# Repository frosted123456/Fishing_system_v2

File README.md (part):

# Ice Fishing Tip-Up Mesh (v2)

Tip-up alarm and per-hole sonar for ice fishing. Each tip-up reports a bite to the chalet box, which rings and
shows everything on its screen and on a phone or PC web page.

| | |
|---|---|
| Firmware | v2, D82 (2026-10-22) |
| Branch | `v2/phase1-mesh-core` |
| Boards | Heltec WiFi LoRa 32 V3, ESP32 WROOM DevKit V1 (30-pin), ESP32-C3 Super Mini (v1 head) |

## Contents

1. [Scope](#1-scope)
2. [System overview](#2-system-overview)
3. [Material](#3-material)
4. [Installation](#4-installation)
5. [Setting up on the ice](#5-setting-up-on-the-ice)
6. [Functions](#6-functions)
7. [Range test](#7-range-test)
8. [How the LoRa airtime is shared](#8-how-the-lora-airtime-is-shared)
9. [Troubleshooting](#9-troubleshooting)
10. [Serial commands](#10-serial-commands)
11. [Repository layout](#11-repository-layout)
12. [Credits](#12-credits)

---

## 1. Scope

Covers building, flashing, wiring, setting up and using the system: tip-ups, hubs, relays and the chalet box.
Not covered: the 3D-printed parts (files kept outside this repo, pictures in 2.1) and the custom sonar board (not built).

**Terms**

| Term | Meaning |
|---|---|
| Chalet box (offshore module) | The Heltec with the screen, buzzer, GPS and CardKB. Runs the network and the web page. Stays in the chalet or is carried on the ice. |
| Hub | A Heltec on the ice with its own hole. Collects the tip-ups around it (its pocket) and sends them to the chalet: ESP-NOW when close, LoRa otherwise. |
| Pocket | A hub and the tip-ups around it (holes within ~50 m). |
| Tip-up | A WROOM board on one hole. Talks ESP-NOW to the nearest hub, sleeps between events. |
| LoRa tip-up | A Heltec on a hole with no pocket around it. Talks LoRa straight to the chalet. |
| Relay | A Heltec that passes a far hub's traffic to the chalet. One hop max. |
| FISH ON | A trip: the spool turned. |

## 2. System overview

| Role | Board | Flash as | Own hole | Sonar |
|---|---|---|---|---|
| Chalet | Heltec V3 | `chalet` | no | no (shows the others) |
| Hub | Heltec V3 | `hub` | yes | optional (`--sonar`) |
| LoRa tip-up | Heltec V3 | `sensor_lora` | yes | optional (`--sonar`) |
| Relay | Heltec V3 | `relay` | no | no |
| Tip-up | ESP32 WROOM | `tipup_wroom` | yes | optional (`--sonar`) |
| Tip-up (v1 head) | ESP32-C3 | `tipup_c3` | yes (reed) | no |

Hub or LoRa tip-up? Same board, same wiring. WROOM tip-ups around it = hub. Alone = LoRa tip-up.

### 2.1 Tip-up pod (3D model)

Printed pod on a Berkley tip-up: battery box with the sonar shield, mast with the board head about 20 cm above the
ice, sliding arm with the Hall sensor, magnet clamp on the shaft. Model v3.0.1, will change.

## 3. Material

### 3.1 Chalet box

| Qty | Item | Note |
|---|---|---|
| 1 | Heltec WiFi LoRa 32 V3 + 915 MHz antenna | OLED is on the board |
| 1 | Active buzzer (CLT1036 or similar) | GPIO7. Passive works too: Settings → Buzzer type |
| 1 | M5Stack CardKB | I2C on GPIO41 (SDA) / GPIO42 (SCL). Optional but needed for the menu and GPS pinning |
| 1 | GPS module, GT-U7 / NEO-6M class | Optional. See 4.4.4 |
| 1 | Small transistor (low-side switch for the GPS GND) | Optional: GPS GND can go straight to GND |
| 1 | 1S LiPo on the Heltec JST, or USB power | Charges from USB-C |

### 3.2 Hub or LoRa tip-up

| Qty | Item | Note |
|---|---|---|
| 1 | Heltec WiFi LoRa 32 V3 + 915 MHz antenna | |
| 1 | 3 × AA Energizer L91 pack with switch | |
| 1 | TPS63020 buck-boost, set to 3.3 V | Feeds the Heltec 3V3 pin |
| 1 | US1881 Hall latch + 4 × N52 magnets | Magnets in the shaft clamp at 45/135/225/315°, poles alternating. Or a reed switch (4.4.5) |
| 1 | 12 mm waterproof push button | Arming button, GPIO5 to GND |
| 2 | 100 k resistors (2:1 divider) | Pack voltage to GPIO2 |
| | Sonar add-on (3.4) | Optional |

### 3.3 WROOM tip-up

| Qty | Item | Note |
|---|---|---|
| 1 | ESP32 WROOM DevKit V1, 30-pin | |
| 1 | 3 × AA Energizer L91 pack with switch | |
| 1 | TPS63020 buck-boost, set to 3.3 V | |
| 1 | US1881 Hall latch + 4 × N52 magnets | Same as the hub |
| 1 | 12 mm waterproof push button | GPIO33 to GND |
| 2 | 100 k resistors (2:1 divider) | Pack voltage to GPIO34 |
| | Sonar add-on (3.4) | Optional |

### 3.4 Sonar add-on (per hole)

| Qty | Item | Note |
|---|---|---|
| 1 | Open Echo TUSS4470 shield 002 | |
| 1 | 200 kHz transducer, BBDM-40200K-DA | 14° beam |
| 1 | **30 V build (4.4.6, what the wiring pictures show):** XL6009 boost module set to 31.5 V + DB107 bridge rectifier + 1N4148 + one 47-100 kΩ resistor + 20 cm of 30 AWG wire (converter enable wire) | ~60 V p-p on the transducer, and the converter is switched off while each ping listens: receiver floor −75 → −86 dB (measured on hub 1). Not an XL6019 (180 kHz switching sits in the sonar band) |
| or 1 | **20 V build:** MT3608 boost, set to 21.5 V | Into J4 middle pin only. 40 V p-p on the transducer, no enable wire. The firmware adapts by itself (4.4.6, mixed fleet) |

### 3.5 Software

| Item | Note |
|---|---|
| VS Code + PlatformIO extension (or `pio` CLI) | Builds and uploads |
| Python 3 | `tools/flash.py` |
| USB-C cable (Heltec), micro-USB (DevKit) | |
| Serial monitor at 115200 | Included in PlatformIO |

## 4. Installation

### 4.1 Get the code

```
git clone https://github.com/frosted123456/Fishing_system_v2
cd Fishing_system_v2
git checkout v2/phase1-mesh-core
```

### 4.2 Cabin Wi-Fi (optional, chalet only)

Copy `src/lora_node/secrets.example.h` to `src/lora_node/secrets.h` and fill in the network name and password.
`secrets.h` is never committed.

Skip it and the chalet runs on its own hotspot. You can also set the Wi-Fi later:

- OLED: Settings → Wi-Fi → Choose network (CardKB)
- Serial: `WIFI:name:password`

### 4.3 Flash a board

1. Plug the board in USB.
2. Open `tools/flash.html` in a browser, pick the board and its job. It gives the command.
3. Run it. Example:

```
python tools/flash.py chalet --id 100 --name "Chalet" --port COM7 --monitor
python tools/flash.py hub --id 1 --name "Pointe" --sonar --gate --port COM8
python tools/flash.py tipup_wroom --id 11 --name "Baie" --sonar --port COM9
```

| Option | Use |
|---|---|
| `--id N` | 1-100, unique on the network |
| `--name "..."` | Name shown everywhere (can be changed later on the page) |
| `--sonar` | Board has the TUSS4470 shield (`tipup_wroom`, `hub`, `sensor_lora`) |
| `--gate` | 30 V build with the converter enable wire (4.4.6): the converter is switched off while each ping listens. Needs `--sonar`. Stays in `devices.ini` for later re-flashes of that board. Leave it out on a board without the wire |
| `--bench` | Bucket test build: sonar runs from boot, `BENCH` line every 2 s (`tipup_wroom`, `hub`). Includes `--sonar` |
| `--build-only` | Build, no upload |
| `--port` | COM port. Leave out and PlatformIO guesses |
| `--monitor` | Open the serial monitor after the upload |
| `--env <name>` | Re-flash a board already in `devices.ini` |

Each board is saved in `devices.ini`. To re-flash the same board: `python tools/flash.py --env hub1_sonar --port COM8`.

ID suggestion: chalet 100, hubs 1-9, tip-ups 11, 12 (pocket 1), 21, 22 (pocket 2)..., relays 90+. A hub's own hole uses the hub's ID.

> **Flash order after a firmware update: every hub and LoRa tip-up first, the chalet last.**

#### 4.3.1 Update a hub without the cable

For a hub that is closed or already on the ice. The first flash with this function has to be over USB.

| Step | Where | What |
|---|---|---|
| 1 | PC | Open `tools/flash.html`, pick the same board, role, node ID and options as the hub runs, tick **Build an update file**, give a folder. Run the command: the file `hub<N>..._date_time.bin` lands in that folder. Copy it to the phone (or do step 3 from the PC) |
| 2 | Hub | Put it in update mode: chalet page, Settings, Advanced, **Firmware update**; or type `OTA` on its serial port; or hold its arming button 3 s while switching it on. Its screen shows the hotspot name |
| 3 | Phone | Join the hotspot `IceFish-Hub<N>-UPDATE` (same password as the others), open `http://192.168.4.1`, pick the file, **Send and restart** |

In update mode the hub does nothing else: no sonar, no alerts, no radio. It leaves the mode by itself after 10 minutes
without an upload. The running firmware is kept in the other slot: a file built for another board (other node ID or
role) is refused, and a new firmware that does not stay up 90 s in three starts is abandoned for the old one. The
chalet box has a single firmware slot (map storage took the other) and is still updated over USB; the tip-ups too.

### 4.4 Wiring

#### 4.4.1 WROOM tip-up + shield 002

| # | ESP32 DevKit V1 | Shield 002 | Signal |
|---|---|---|---|
| 1 | **3V3** (TPS63020 3.3 V) | **5V** pin | TUSS4470 VDD. **Never 5 V.** |
| 2 | GND | GND | Common ground (pack, TPS63020, boost module, ESP32, shield) |
| 3 | D18 | D13 | SCLK |
| 4 | D19 | D12 | SDO → MISO |
| 5 | D23 | D11 | MOSI → SDI |
| 6 | D5 | D10 | NCS |
| 7 | D26 | D8 | IO1 |
| 8 | D25 | D9 | IO2 (burst) |
| 9 | VP (GPIO36) | A0 | VOUT echo. Twist with its own GND wire |
| 10 | - | **J4 middle pin**, no jumper on J4 | Boost output + (wire A): XL6009 at 31.5 V, or MT3608 at 21.5 V. Boost GND to shield GND |
| 11 | - | **C6, the pad nearer the TUSS4470** | 30 V build only: wire B from the XL6009 output through DB107 + 1N4148, and the bleed resistor across C6 (4.4.6) |
| - | not wired | D2, D3, RESET, AREF, 3.3V, VIN | |

Other WROOM connections:

| Pin | To |
|---|---|
| GPIO27 | Hall latch OUT. US1881 VDD from the **pack**, not 3.3 V |
| GPIO33 | Arming button to GND (no resistor) |
| GPIO34 | 2:1 divider from the pack |
| GPIO2 | LED (on the DevKit) |
| D13 (GPIO13) | 30 V build: converter enable wire to the XL6009's chip pin 2 (4.4.6). Flash with `--gate`. Not yet tried on a WROOM |

#### 4.4.2 Heltec V3 + shield 002 (hub, LoRa tip-up)

| # | Heltec V3 | Shield 002 | Signal |
|---|---|---|---|
| 1 | **3.3V** pin | **5V** pin | TUSS4470 VDD. **Never 5 V.** |
| 2 | GND | GND | Common ground |
| 3 | GPIO47 | D13 | SCLK |
| 4 | GPIO33 | D12 | SDO → MISO |
| 5 | GPIO48 | D11 | MOSI → SDI |
| 6 | GPIO34 | D10 | NCS |
| 7 | GPIO38 | D8 | IO1 |
| 8 | GPIO39 | D9 | IO2 (burst) |
| 9 | GPIO6 | A0 | VOUT echo. Twist with its own GND wire |
| 10 | - | **J4 middle pin**, no jumper on J4 | Boost output + (wire A): XL6009 at 31.5 V, or MT3608 at 21.5 V. Boost input from the pack |
| 11 | - | **C6, the pad nearer the TUSS4470** | 30 V build only: wire B from the XL6009 output through DB107 + 1N4148, and the bleed resistor across C6 (4.4.6) |
| - | not wired | D2, D3, RESET, AREF, 3.3V, VIN | |

Other Heltec connections:

| Pin | To |
|---|---|
| 3.3V pin | TPS63020 3.3 V output |
| GPIO4 | Hall latch OUT (or reed, 4.4.5). US1881 VDD from the pack |
| GPIO5 | Arming button to GND |
| GPIO2 | 2:1 divider from the pack (not the onboard VBAT pin) |
| GPIO7 | Buzzer (optional on a hub) |
| GPIO40 | 30 V build: converter enable wire to the XL6009's chip pin 2 (4.4.6). Flash with `--gate` |

Turn the pack off when USB is plugged in.

#### 4.4.3 Shield 002 set-up

- Frequency jumpers: **JP3 + JP4 only** (200 kHz). JP1, JP2, JP5, JP6 open.
- Transducer: cable shield → **top** pin, signal → bottom pin.
- Boost output into the **J4 middle pin** only. Not VIN, not the XT30.
- 30 V build: XL6009 at **31.5 V**, wire B, bleed resistor and enable wire, see 4.4.6.
- 20 V build: MT3608 at **21.5 V** (max ~22 V), nothing else.
- Optional: remove R3 (power LED).

#### 4.4.4 Chalet box (offshore module)

| # | Heltec V3 | To | Signal |
|---|---|---|---|
| 1 | JST battery | 1S LiPo 3.7 V | Power. Charges from USB-C |
| 2 | 3.3V pin | GPS VCC, CardKB VCC | 3.3 V out |
| 3 | GND | GPS switch, CardKB GND, buzzer − | Common ground |
| 4 | GPIO48 | GPS TXD | GPS → Heltec (9600 baud) |
| 5 | GPIO47 | GPS RXD | Heltec → GPS |
| 6 | GPIO26 | Transistor gate/base | GPS power on (driven high). GPIO46 is driven too |
| 7 | GPIO41 | CardKB SDA | I2C |
| 8 | GPIO42 | CardKB SCL | I2C |
| 9 | GPIO7 | Buzzer + | Active buzzer (CLT1036) |
| - | GPIO2, 4, 5 | not wired | Hole sensor, button and divider are for hubs only |

On the board, nothing to wire: PRG button (GPIO0), OLED, LoRa radio, battery reading (GPIO1/37), LED.

- CardKB VCC on 3.3 V is est.: check your box (the CardKB also takes 5 V).
- GPS GND straight to GND (no transistor): build with `-D GPS_EN_PIN=-1`.
- No GPS: build with `-D GPS_RX_PIN=-1`.
- GPS on other pins: the chalet scans the free header pins at boot and keeps the one that answers.

#### 4.4.5 Reed switch instead of the Hall sensor

A reed switch can replace the Hall latch to detect FISH ON. The code is still active (the C3 tip-up uses it).

| Board | Wire | Build flag (add to the board in `devices.ini`) | Polarity |
|---|---|---|---|
| Heltec hub / LoRa tip-up | Reed between GPIO4 and GND | `-D HOLE_HALL_LATCH=0` | OLED Settings → Reed polarity |
| WROOM tip-up | Reed between GPIO27 and GND | `-D HALL_LATCH=0` | `REED_ACTIVE_HIGH` in `src/sensor_node/config.h` |
| C3 tip-up | Reed between GPIO4 and GND | none (reed by default) | `REED_ACTIVE_HIGH` |

Default polarity: trips when the pin goes HIGH (contact opens). With a reed, the trip follows the switch level, not
spool turns.

#### 4.4.6 30 V drive and converter enable wire (external VDRV, knob `vmode 2`)

Two changes that go together. They are the build the wiring pictures of 4.4.1 and 4.4.2 show.

- **30 V drive.** The TUSS4470's own drive regulator stops at 20 V (40 V p-p). Feeding its VDRV pin from outside at
  ~30 V gives ~60 V p-p on the transducer, **+3 to +4.6 dB (est.)**. No new board; `vmode 2` is the default.
- **Converter enable wire.** The XL6009 switches at 400 kHz and the receiver hears it at −75 dB. One wire from an ESP32
  pin to the converter's enable pin lets the firmware switch it off while each ping listens: receiver floor **−86 dB**
  in water, with no loss of transmit strength (measured on hub 1, 14 Nov 2026, D179).

| # | From | To | Note |
|---|---|---|---|
| 1 | Pack + / GND | XL6009 IN + / IN − | Replaces the MT3608. **Set the output to 31.5 V with a meter before connecting anything** |
| 2 | XL6009 OUT + | Shield **J4 middle pin** (wire A) | Same pin as the MT3608 today; no jumper on J4. Becomes VPWR ≈ 30.7 V after the shield's 1N4001 |
| 3 | XL6009 OUT + | DB107 **−** leg | DB107: use only − and +, cut the two ~ legs |
| 4 | DB107 **+** leg → **1N4148** (stripe toward C6) | Shield **C6, the pad closer to the TUSS4470** (wire B) | VDRV ≈ 29.6 V. The other C6 pad is GND (beeps to ground) |
| 5 | XL6009 OUT − | Shield GND | Common ground |
| 6 | Shield **C6, the pad closer to the TUSS4470** | The **other C6 pad** (GND), through a **47-100 kΩ resistor** soldered across C6, pad to pad (bleed) | Drains C6 when the power goes off, see below. Draws 0.3-0.65 mA at 30 V (about 3-7 mA from the pack, est.) |
| 7 | XL6009 **chip pin 2** (EN), cut free of its pad | Heltec **GPIO40** / WROOM **D13** (enable wire, 30 AWG, no resistor) | See "Converter enable wire" below. Flash with `--gate` |

Rule: **VPWR > VDRV + 0.3 V at all times, power-up included** (datasheet 6.3 note / 7.3.1: otherwise reverse current
flows from VDRV into VPWR). VPWR draws only 150-340 µA, so the shield's 1N4001 drops just ~0.45-0.5 V; VDRV idles at
microamps, where the DB107's two diodes drop only ~0.7-0.8 V (est.): ~0.25 V gap, too tight. The 1N4148 adds ~0.4-0.6 V:
**~0.7-1 V gap** for ~−0.2 dB. Never wire B without the DB107 + 1N4148.

Power-off (D143): the diodes of wire B stop C6 from discharging backwards, and nothing loads VDRV in this mode, while
VPWR follows the boost output down. Without the bleed resistor (row 6) VDRV stays near 30 V with VPWR falling under it
at every switch-off: the reverse-current case of the rule above. With 47-100 kΩ, C6 empties in 0.1-0.2 s, faster than the
boost output falls. The bleed also keeps 0.3-0.65 mA flowing in the DB107 + 1N4148 while idle, so their drop is a real
~1.5 V (est.) instead of a microamp-level one: the gap no longer depends on leakage. It has no effect on a ping.

Pads on the shield (from the board file `referance/shield002_tmp/TUSS4470_shield.kicad_pcb`): C6 lower pad = VDRV,
C6 upper pad = GND, R1 lower pad = VPWR (an easier meter point than C7).

**Converter enable wire** (D170 to D179). The usual XL6009 module (XL6009E1, 47 µH, 100 µF output, 330 Ω + 10 k trimmer
feedback) has no enable pad: chip pin 2 (EN) is tied to VIN on the board.

1. Meter check: legs toward you, chip seen from the top, pins are 1 GND, 2 EN, 3 SW, 4 VIN, 5 FB. Pin 2 beeps to pin 4.
2. Cut pin 2 free of its pad (or unsolder and lift it). It must no longer beep to pin 4.
3. Solder a thin wire (30 AWG) from the lifted pin to **GPIO40** (Heltec) or **D13** (WROOM). No resistor (a large
   series resistor may not pull the pin low enough against its internal pull-up).
4. Flash with `--gate`: the firmware then drives the pin HIGH while the sonar runs and LOW in sleep. **Do not leave the
   wire on a board flashed without `--gate`:** the pin then floats, and on Hole 2's module a floating enable left the
   converter off (output at the pack voltage, wiring check "VDRV NOT READY"), although the datasheet says floating = on.
5. Web page → Settings → Advanced → Wiring check: **Converter enable wire OK, noise floor N dB lower with the converter
   switched off** (hub 1: 14 dB or more). `NO EFFECT` = the pin is still tied to VIN, or the wire is on another GPIO.
6. Bench build: the **Converter off 6 s** button holds the converter off: the transmit fades within 1-2 s and comes back
   (the pack voltage still reaches the driver through the converter's coil and diode, so the strongest echoes stay). The
   **Noise scan** button records the receiver floor with the converter running and gated, step by step.

What the firmware does with the wire: converter off 0.3 ms before each burst, on again after the last sample of its
listening window (about 21 ms), so the 100 µF output capacitor has lost nothing when the burst fires; in sleep the
converter stays off. The rule VDRV below VPWR holds: both follow the same rail. Not yet tried on a WROOM (same driver).

Battery (est., from the module's parts): the feedback divider alone draws 3.8 mA at 30 V and the bleed 0.3-0.65 mA; with
the chip's 2.5-5 mA that is about 35-40 mA from the pack while the converter runs, against ~2-3 mA for the MT3608. With
the enable wire the converter is off whenever the board sleeps (about 0.5 mA left through the divider). Datasheet
minimum input 3.6 V: the end of the pack.

Bring-up:

1. Meter, diode mode: DB107 − to + reads 1.0-1.3 V, reversed OL.
2. **Check the gap before wire B touches C6.** Connect wire A only, power on, sonar pinging (`vmode 0`, the chip makes
   its own 20 V: safe). Measure VPWR on the **C7** pad that is not GND (small capacitor just left of C6). Measure the
   1N4148 end of the DB107 chain, unconnected (worst case: no current). Gap = VPWR − that end. **≥ 0.5 V: connect wire B.** Less: add
   a second 1N4148.
   Then wire B on: C6 pad must read below C7.
3. `vmode 2` is the default since D147 (nothing to set after a flash; the Water presets do not touch it).
   Then the enable wire, steps 1 to 5 above.
4. Bench line: no `BURST FAULT`. `ring=` a bit longer: raise `dead` one step if needed. (No `VDRV LOW` in this mode.)
5. Gain check: measure echo **minus floor** (bottom, a weight) **before wire B goes on** (20 V drive) and after
   (`vmode 2`): expect +3 to +4.6 dB. With wire B connected, `vmode 0` does NOT go back to 20 V.

**Mixed fleet** (knobs are global: the hub broadcasts the same `vmode` to every pod). The enable wire is per board
(`--gate`): a board flashed without it simply leaves its converter running. `vmode 2` on a pod WITHOUT wire B
leaves its VDRV unpowered (weak pings). Since D163 such a board notices it by itself (no transmit seen on 8 pings in a
row), prints `SONAR: no transmit seen in external-VDRV mode` and runs on the chip's regulator until the next boot
(written from the datasheet behaviour, **not yet tried on a board without wire B**). If an unmodded pod still pings
weakly, keep **`vmode 0` everywhere**: modded pods
still drive at ~30 V (the chip's 20 V regulator only charges and stays off above its target; inferred, confirm once:
same echo, no `BURST FAULT` with `vmode 0` and `vmode 2` on a modded hub). WROOM pods: same shield, same wiring, knobs
from the hub; `TUNE` runs on the Heltec only.

Limits: chip 36 V max (40 V absolute), C6 rated 40 V, XL6009 output caps often 35 V: stay at **31.5 V**.
Back to 20 V: `vmode 0` **and** unplug wire B (with wire B in place VDRV stays ~30 V; safe, not 20 V).
The XL6009 must still make ≥ 29 V on a half-used pack; if not, keep the MT3608 at 12 V in front of it.

### 4.5 Bench check

| Step | Do | Expect |
|---|---|---|
| 1 | Power the chalet alone | Boot screen, then Home |
| 2 | Power a hub | Chalet Home shows the pocket within a few seconds |
| 3 | Power a tip-up | 2 quick blinks at boot. It starts armed |
| 4 | Turn the spool a quarter turn | FISH ON on the chalet, buzzer, phone |
| 5 | Web page → Settings → Advanced → Wiring check → Run | Sensor, button, battery, sonar shield, radio OK. A sleeping tip-up answers within 1 min. 30 V build with `--gate`: "Converter enable wire OK" |
| 6 | Sonar holes: flash with `--bench`, transducer in a bucket | `BENCH` line every 2 s on serial, bottom found |

## 5. Setting up on the ice

1. Mount every board **at least 20 cm above the ice**.
2. Turn on the devices in any order as you set the holes. The chalet shows "SETUP" until a hub has been in for
   5 min (10 min max after boot). That is normal.
3. Check every hole is armed (no DISARMED on the page or OLED). Holes keep their armed state across reboots.
4. Connect the phone (6.3).
5. Place the holes on the map:
   - With GPS: carry the chalet box to each hole, OLED → GPS / pin holes, select the hole, Enter.
     Or on the page: tap the hole → **Pin here**.
   - Without GPS: on the page, tap the hole → **Tap the map**.
6. Set the bait depth of each sonar hole: tap the hole → bait.
7. Check bait: disarm the hole first (short press), re-arm after.
8. Fresh battery pack in a hub or tip-up: hold its arming button while switching the pack on, until the LED blinks 3
   times (~3 s), or on the chalet page: Test tab → **Battery packs** → **New pack** on that hole. That sets its pack
   hours back to 0. **Read all holes** there shows every hub and tip-up (flagged past 12 h); the hub OLED shows its own
   at the top right (`Pk7.3h`); `PACK` on serial or the bench page too. Released sooner = ordinary start.

**Battery (3 × L91 per module, est. from datasheets, D205):** about 15-24 h per pack at 20 °C, 11-21 h at -15/-20 °C,
about 10 h with the bench page streaming. Plan one fresh pack per module per session plus one spare. The L91 voltage
stays flat until the last 10-15 %, so the pack hours, not a voltage, are the gauge; a meter on the 10 A range in
series with the pack gives the real figure (hours = ~13 Wh / pack watts).

The first time, the map origin is set by itself once the chalet GPS is steady for 30 s. It is kept after that.
To move it: OLED GPS page → Chalet here, or tap the chalet on the map → **Chalet here**. Pinning a hole needs a GPS
fix and an origin.

## 6. Functions

### 6.1 Tip-up

| Action | Result | LED |
|---|---|---|
| Short press | Arm / disarm | Armed: 2 short. Disarmed: 1 long |
| Short press while tripped | Clear the trip | 1 short |
| Hold 3 s | Send a status report now | 3 short |
| Held while switching the pack on, ~3 s | New pack: pack hours back to 0 (D205) | 3 blinks |
| Spool turns a quarter turn | FISH ON | |
| Spool still for 30 s | Line back to normal on the tip-up | |

A disarmed hole ignores the spool (use it to check the bait). Disarming a tripped hole also clears the alarm on
the chalet. Clearing a trip at the hole does not: the chalet keeps ringing until silenced.

Holes start armed and keep their state across reboots. The hub and LoRa tip-up button (GPIO5) works the same,
with the white LED and a short chirp. LED also blinks once per status sent and 3 times per alert sent.

### 6.2 Chalet box and hubs (OLED)

**PRG button**

| Press | Chalet | Hub |
|---|---|---|
| Short | Next page. During FISH ON: silence. Screen asleep: wake it | Same |
| Double | Page action (written at the bottom). On Home: unsilence | Same |
| Hold 3 s | Connect phone page | Hotspot on/off (30 min, +5 min while a phone is on it) |
| Hold 10 s | Network reset (link, channel and relays back to default; names, alerts and Wi-Fi kept) | Same |

A bar shows what releasing will do (from 1 s). Pages go back to Home after 60 s (Settings 3 min). The screen
sleeps after 5 min and wakes on FISH ON or any press. GPS pinning and Wi-Fi options need the CardKB.

**CardKB (chalet)**

| Key | Does |
|---|---|
| Esc | Menu. In a page: back to the menu |
| ← / → | Previous / next page |
| ↑ / ↓ | Inside the page (more holes, next hole, list) |
| Enter | Page action ("OK: ..." at the bottom) |
| Space / Tab / n, p | Next / previous page |
| + / − / a | Sonar and Focus: depth scale (a = auto) |
| S | Silence on/off |
| Any key during FISH ON | Silence |
| Del, twice | GPS page: clear the selected hole's position |

**Pages**

| | |
|---|---|
|  | **Menu** (Esc). All pages. |
|  | **Home**. Holes online, one row per pocket (filled = OK, hollow = offline, half = low battery, X = sensor fault, blinking = FISH ON). Link per pocket: OK (LoRa), ESP-NOW, n off, LOST. Footer: near bait, battery low, range test. |
|  | **FISH ON**. Takes over every page, blinks until silenced. |
|  | **Holes**. 4 per page: name, fish seen by the sonar, battery. ↑ / ↓ for more. |
|  | **Sonar**. One column per sonar hole: bottom, fish (bars), bait (tick). |
|  | **Focus**. Fish finder of the watched hole, last ~30 s. ↑ / ↓ = other hole. |
|  | **GPS / pin holes**. Chalet here = map origin. Select a hole, Enter = pin it where the box is. |
|  | **Network**. Link, LoRa channel and activity, signal of each hub (E = via ESP-NOW). |
| | **Test / simulation**. Holes running fake sonar or fake trips, radio test. |
|  | **Connect phone**. Wi-Fi name, password and address. |
|  | **Settings**. Wi-Fi, buzzer, near-bait beep, alarm, LoRa channel, simulation, sonar filter, display, network reset, reboot. |
|  | **Hub Home**. Link to the chalet, its holes and battery. Hub pages: Home, Holes, Network, Connect, Settings (hotspot, buzzer, alarm, ESP-NOW relay, reed polarity, network reset, reboot). |
|  | **Hub Connect**. Hold PRG 3 s to turn the hub hotspot on. |

### 6.3 Web page

**Connect**

| Where | Wi-Fi | Address |
|---|---|---|
| Chalet hotspot | `IceFish-Remote`, password `fishon123` | http://192.168.4.1 |
| Cabin Wi-Fi (secrets.h or Settings → Wi-Fi) | Same network as the chalet | The address on the OLED Connect page, or http://icefish.local |
| Hub hotspot (hold PRG 3 s) | `IceFish-Hub<N>`, password `fishon123` | http://192.168.4.1 |

`icefish.local` works on most PCs and iPhones. Some Android phones need the number address.

Works in a phone or PC browser. Tap once on the page to allow the alert sound.

On every tab: status line, **Sound on/off**, **Silence alerts**, and a red FISH ON bar at the bottom with the hole names.

**Holes tab**

| Item | Does |
|---|---|
| Pocket map | Drag to pan, pinch or +/− to zoom, ⌂ = back to the chalet, ⤢ = full screen |
| Map / Satellite | Background (needs internet on the phone, or a saved area) |
| Depth | CHS bathymetry where it exists |
| Save area | Keeps the tiles of what you see on the chalet, for any phone on the ice |
| Cyan ring | Hole being followed (see Sonar tab). Arrow = it just moved there. Padlock = your pick |
| Tap a hole | Sheet: bottom, fish, bait, line out, battery, link, distance. Arm / Disarm, bait, Watch sonar, Pin here, Move, Remove |
| Tap the chalet | Chalet here, clear all positions |
| Live card | Beside the map: the whole water column of every streaming hole, newest on the right. Bottom, fish, bait line. Follow the action button and the 1 / 2 / 3 picker: how many holes stream at once (more = more radio, slower page). Tap a panel for the full view on the Sonar tab |
| Hole cards | Folded under the Live card. State, battery, link, last minutes of sonar. Watch, Set bait, Arm / Disarm, Rename |

**Sonar tab**

| Item | Does |
|---|---|
| Follow the action | On by default. The live view goes to the hole with the most action. FISH ON wins for 2 min. Up to 2 more holes stream at the same time when the radio has room ("LIVE too") |
| Hole cards on top | Every sonar hole with its water-column preview. Tap one to watch it live; your pick stays 5 min, then Follow takes over again |
| Flasher | Live, about 1 s behind. Pause to freeze |
| Last 60 seconds | Waterfall, 4 pings per second. With **Raw echogram** on (Display, default on), the hole you watch also sends its raw ping once a second (the HD line: 2.5 cm cells at any depth, 1 dB steps near the noise floor) with a crisp mark for each echo (up to 12, at its exact depth; in a hole deeper than 6 m the marks cover the bottom 6 m), and the waterfall shows it underneath the detector's marks, like a fish finder: an echo the detector did not report is still visible. Water (anything under the **Weak echoes** level: 4 / 8 / 12 / 20 dB over the floor; full colour at 40 dB) stays dark, the blind zone is a flat grey band, below the bottom is dimmed (second bottom echo, barrel walls). A still object (a hanging ball, a stump) is reported as a mark for a few seconds only, then becomes part of the still scene; the raw echogram keeps showing it. Off: only what the detector reported |
| ft / m | Depth units on this phone |
| Display | Depth scale, colour gain, weak echoes |
| Processing | Noise filter, water type (lake / shallow / bucket), Advanced, Defaults, Send to holes again |
| Sonar test mode | Fake sonar on the test holes |

**Radio tab**

| Item | Does |
|---|---|
| Links | When the chalet last heard each hub on LoRa and ESP-NOW |
| Range test | See section 7 |
| Radio test modes | Fixed or rotating speed for every hub, adaptive speed (on by default), reset stats |
| Hubs | Speed (SF) used per hub, packets, signal |

**Settings tab**

| Section | Contains |
|---|---|
| Alerts | Chalet buzzer, near-bait beep, FISH ON alarm: until silenced, or 1, 5, 15, 30 min after the trip |
| PIN | Optional 4-8 digit PIN for any change from the page. Silence and Watch never need it |
| Network | Wi-Fi state, link, channel |
| This phone | Alert sound, depth units, sound test |
| Advanced | Line per spool turn, beam angle, wiring check, map storage, LoRa channel, relays, test and simulation |
| About | Version |

Forgot the PIN: serial `PIN CLEAR`.

**Wi-Fi tab**

The chalet keeps up to 4 networks with their passwords (house, parents, cabin). Saved networks: one tap on Connect
switches the chalet; ✕ forgets one. Add a network: name and password, or Scan and tap Use on a network around.
When the network in use is not found, the chalet joins the strongest saved one by itself within a minute or two
(first retry after boot, then every 5 min). Passwords never come back to the page. If your phone is on the cabin
network when you switch, the page comes back at `http://icefish.local` or on the hotspot.

### 6.4 Alerts

| Event | Chalet | Phone |
|---|---|---|
| FISH ON | Screen, buzzer | FISH ON bar, beep |
| Silence (button, key or page) | Sound stops. Holes already back to normal are cleared. A hole still out rings again after 5 min | Same on every phone |
| Line back to normal | Keeps ringing until silenced (default) or the alarm time in Settings | |
| New trip | Always rings, even during a silence | |

### 6.5 Map offline

At home with internet: open the Holes tab, move to the lake, zoom in, **Save area**. The tiles stay on the chalet
(up to ~4.8 MB, shared with the depth pack and range test runs). Tiles seen on a phone also stay on that phone.

Depth contours (optional, PC):

```
pip install numpy rasterio matplotlib pyproj
python tools/lake_prep.py --bbox 45.40 -75.80 45.55 -75.60 --nonna --name "Ottawa-Gatineau" --out season.json
```

Then Settings → Advanced → Map storage → Store on chalet.

## 7. Range test

LoRa only. Gives the success rate of each speed (SF9 to SF5) against distance. SF6 and SF5 need the hub on
firmware D80; older hubs test SF9 to SF7 only.

1. Put the chalet box next to the hub that stays put. It must reach the chalet directly and not relay another hub.
2. Web page → Radio → Range test. Pick the hub.
3. Press **Box is at the hub: pin it here** (needs a GPS fix and the map origin set).
4. Add a note if you want (ice, antenna height...). Press **Start the range test**.
5. Walk away with the box. The banner shows the run on every tab, and the OLED Home footer shows `RANGE <distance> SF<n> ok/--`.
6. Press **Stop**, then **Download CSV**.

The run stops by itself after 2 h, if the hub is not heard for 5 min, or if storage is low. 30 runs max: download
and delete old ones. The other hubs keep working during the test.

During a run the hub-to-chalet link is forced to LoRa (the Radio tab shows it), then goes back to the setting at
stop. Without that, a hub next to the chalet talks ESP-NOW, keeps its LoRa radio idle, and every row reads `ok 0`.
A side-by-side check should show `ok 1` on all five speeds with an RSSI around -20 to -40 dBm within a minute of
starting (the hub needs a few seconds to switch over).

CSV columns: `t_s, utc, lat, lon, sats, hdop, dist_m, frame, mode, ok, crc, rssi_dbm, snr_db, hub_beacon_rssi, hub_beacon_snr, hub_beacon_lost64`.

## 8. How the LoRa airtime is shared

One LoRa channel, one frame of 0.5 s (it stretches to 1, 1.5 or 2 s by itself when the turns don't fit). The chalet
sends a beacon at the start of each frame with the turn of every hub: when, how long, how many bytes, at what
speed. Hubs only transmit in their turn. WROOM tip-ups use ESP-NOW
to their hub, which costs no LoRa time: the hub packs its whole pocket into its own turn.

| Part of the frame | What it is |
|---|---|
| beacon | Chalet → everyone. The plan for this frame, the watched hole, commands |
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
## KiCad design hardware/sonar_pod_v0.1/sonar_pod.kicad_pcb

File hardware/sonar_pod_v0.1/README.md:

# Sonar pod board v0.1 — generated design (NOT ordered, NOT reviewed by a human yet)

TUSS4470 front end (net-for-net from Open Echo `shield_003`, 200 kHz values fixed) + MT3608 boost 22 V for VPWR
(EN from the head, pulled up) + TPS63020 3.3 V + sense dividers + one 16-wire cable to the ESP32 in the head.
52 x 43 mm, 2 layers, all SMD on top, 4 x M3. Made with KiCad 7 tools (opens in KiCad 10).

| File | What |
|---|---|
| `sonar_pod.kicad_pro/.kicad_sch` | schematic, label style (every pin ends in a global label, no wires) |
| `sonar_pod.kicad_pcb` | routed board (freerouting), zones filled, DRC: 0 unconnected, 0 clearance |
| `sonar_pod_schematic.pdf`, `routed_f.png`, `routed_b.png` | previews |
| `sonar_pod_gerbers.zip` | gerbers + drill for JLCPCB |
| `sonar_pod_bom_jlcpcb.csv`, `sonar_pod_cpl_jlcpcb.csv` | assembly BOM (LCSC numbers) and pick-and-place |
| `sonar_pod.step` | 3D (library models only) |
| `src/design.py` | the single source: parts, pins, nets, positions. `make_pcb.py`, `make_sch.py`, `route.sh` regenerate everything |

## Head cable J4 (JST-PH 2.0 mm, 16)
1 3V3 · 2 GND · 3 GND · 4 NCS · 5 SCLK · 6 SDI · 7 SDO · 8 IO1 · 9 IO2 · 10 VOUT · 11 OUT4 · 12 HALL · 13 BOOST_EN · 14 VBAT_ADC · 15 NTC_ADC · 16 VPWR_ADC
ESP32 DevKit V1 side (proposal): NCS 5, SCLK 18, SDI 23 (MOSI), SDO 19 (MISO), IO1 26, IO2 25, VOUT 36, OUT4 32, HALL 27, BOOST_EN 33, VBAT_ADC 35, NTC_ADC 39, VPWR_ADC 34.

## Other connectors
J1 battery (XH 2): + −. J2 transducer (XH 5): A, B, shield(SGND), NTC, NTC-gnd. J3 hall (XH 3): 3V3, GND, OUT.

## Design notes
- VBOOST = 0.6 V x (1 + 360k/10k) = 22.2 V. Knob `vdrv` 20 (VPWR > VDRV + 0.3 V). TVS SMAJ24A on the rail.
- MT3608 EN: 100k pull-up to VB, J4.13 pulls it low to cut the sonar rail (sleep). Boost off = TUSS4470 unpowered: re-init after wake.
- TPS63020: EN = VIN (always on), PS/SYNC = GND (power save on), VINA via 10 R + 100 nF, 1.5 uH XFL4020, 2 x 10 uF in, 3 x 22 uF out, FB 1M/180k.
- Receive: R_INP 200 R 1206 + C_INP 330 pF -> INP; C_INN 22 nF to SGND; C_FLT 3.3 nF to SGND; spare DNP footprints C18/C19 for tuning.
  SGND island (F.Cu) joined to GND through FB1 ferrite (R9 0 R DNP alternative). Transducer shield pin on SGND.
- VOUT to the cable through 100 R + 1 nF. VBAT/2 and VPWR x 10/85 dividers, NTC 10k pull-up.
- Reverse battery: AO3401A P-FET high side, gate to GND through 100k.

## VERIFY BEFORE ORDERING (things I could not check from here)
1. U2 footprint `Texas_DSJ0014A` is GENERATED (pads +-1.45 mm, 0.85 x 0.28, EP 1.6 x 2.6, pins 1-7 left top->bottom,
   8-14 right bottom->top). Compare with the TI DSJ0014A drawing / KiCad 10 library and replace if KiCad 10 has it.
2. D1 (K=1 to VBOOST, A=2 to SW) and D2 (K=1 to VBOOST, A=2 to GND) polarity against the SMA / SOD-123W footprint pad 1.
3. JST pin-1 orientation on J1-J4 against the housings you crimp.
4. L1 saturation current (>1.5 A at 22 V boost from 3.6 V), L2 >4 A. LCSC numbers for L1/L2/FB1/D2/D3/J1-J4 were typed from memory: check each on lcsc.com.
5. Routing is freerouting's: look at the boost loop (L1-U3-D1-C8) and the INP/INN traces in KiCad; shorten by hand if they wander.
6. Silkscreen: 20 overlap warnings (reference text over pads) — cosmetic, clean up or let JLC strip them.
7. ESP32 ADC pins: 34/35/36/39 are input only (fine for ADC), 32/33 are output capable.

## Rough cost (JLCPCB, 5 boards, estimate — verify in the JLC quote)
PCB 5 x 52x43 2-layer ~ $4 · assembly setup + stencil ~ $10 · extended-part fees ~ 8 x $3 = $24 ·
parts ~ $9/board (TUSS4470 $3.1, TPS63020 ~$2.5, inductors ~$0.8, connectors ~$0.7, rest ~$2) x 5 = $45 · shipping ~ $20
=> about $100-120 for 5 assembled boards, ~$22 each. The shield + 2 modules route is ~$40-45 per tip-up.

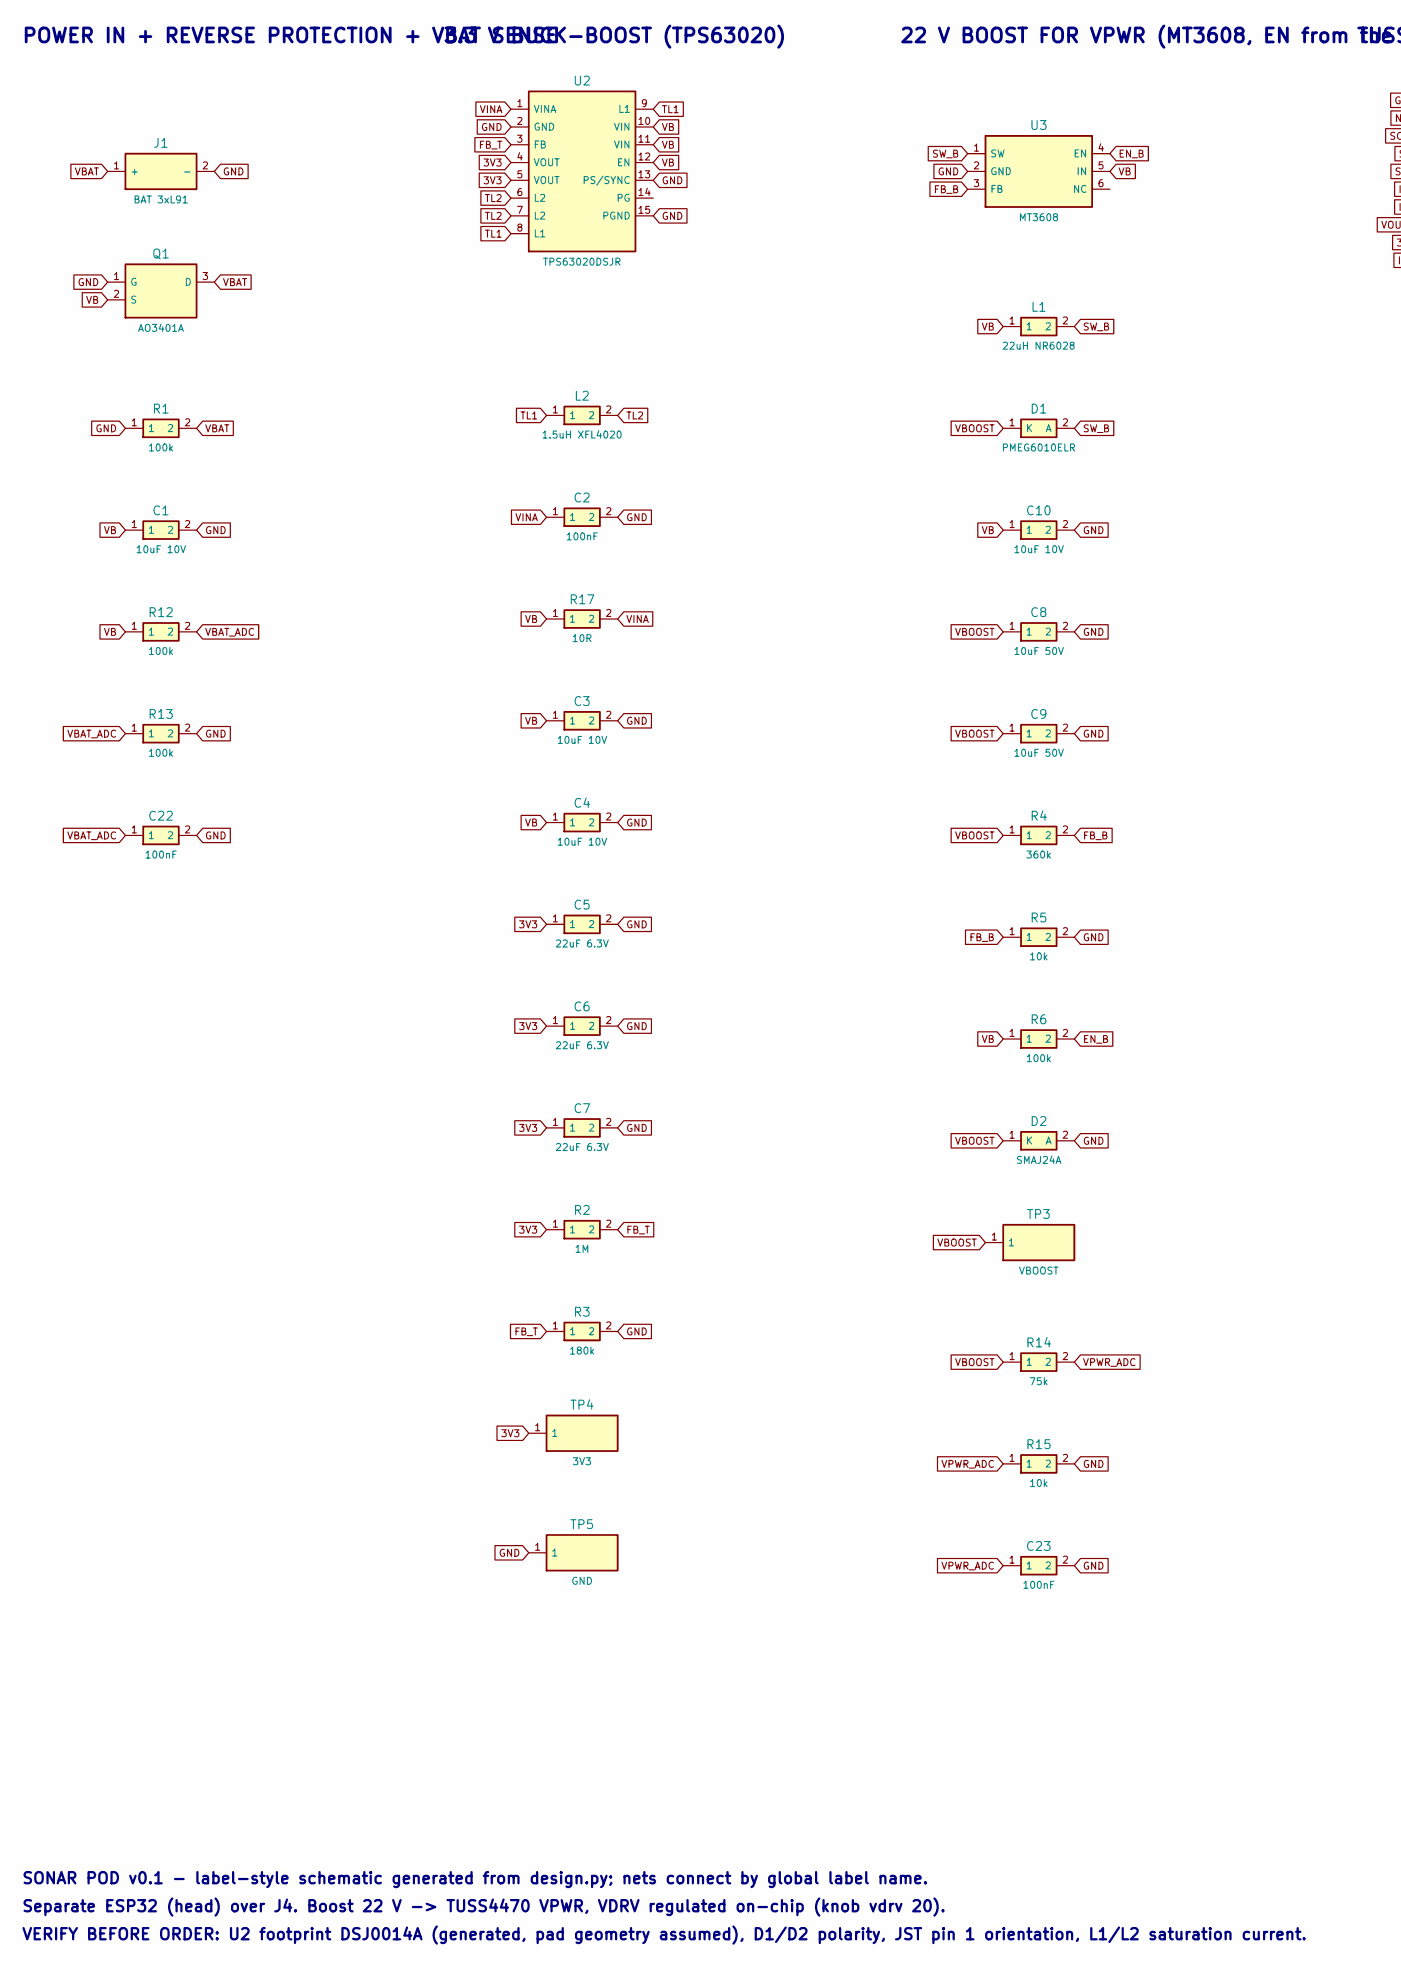
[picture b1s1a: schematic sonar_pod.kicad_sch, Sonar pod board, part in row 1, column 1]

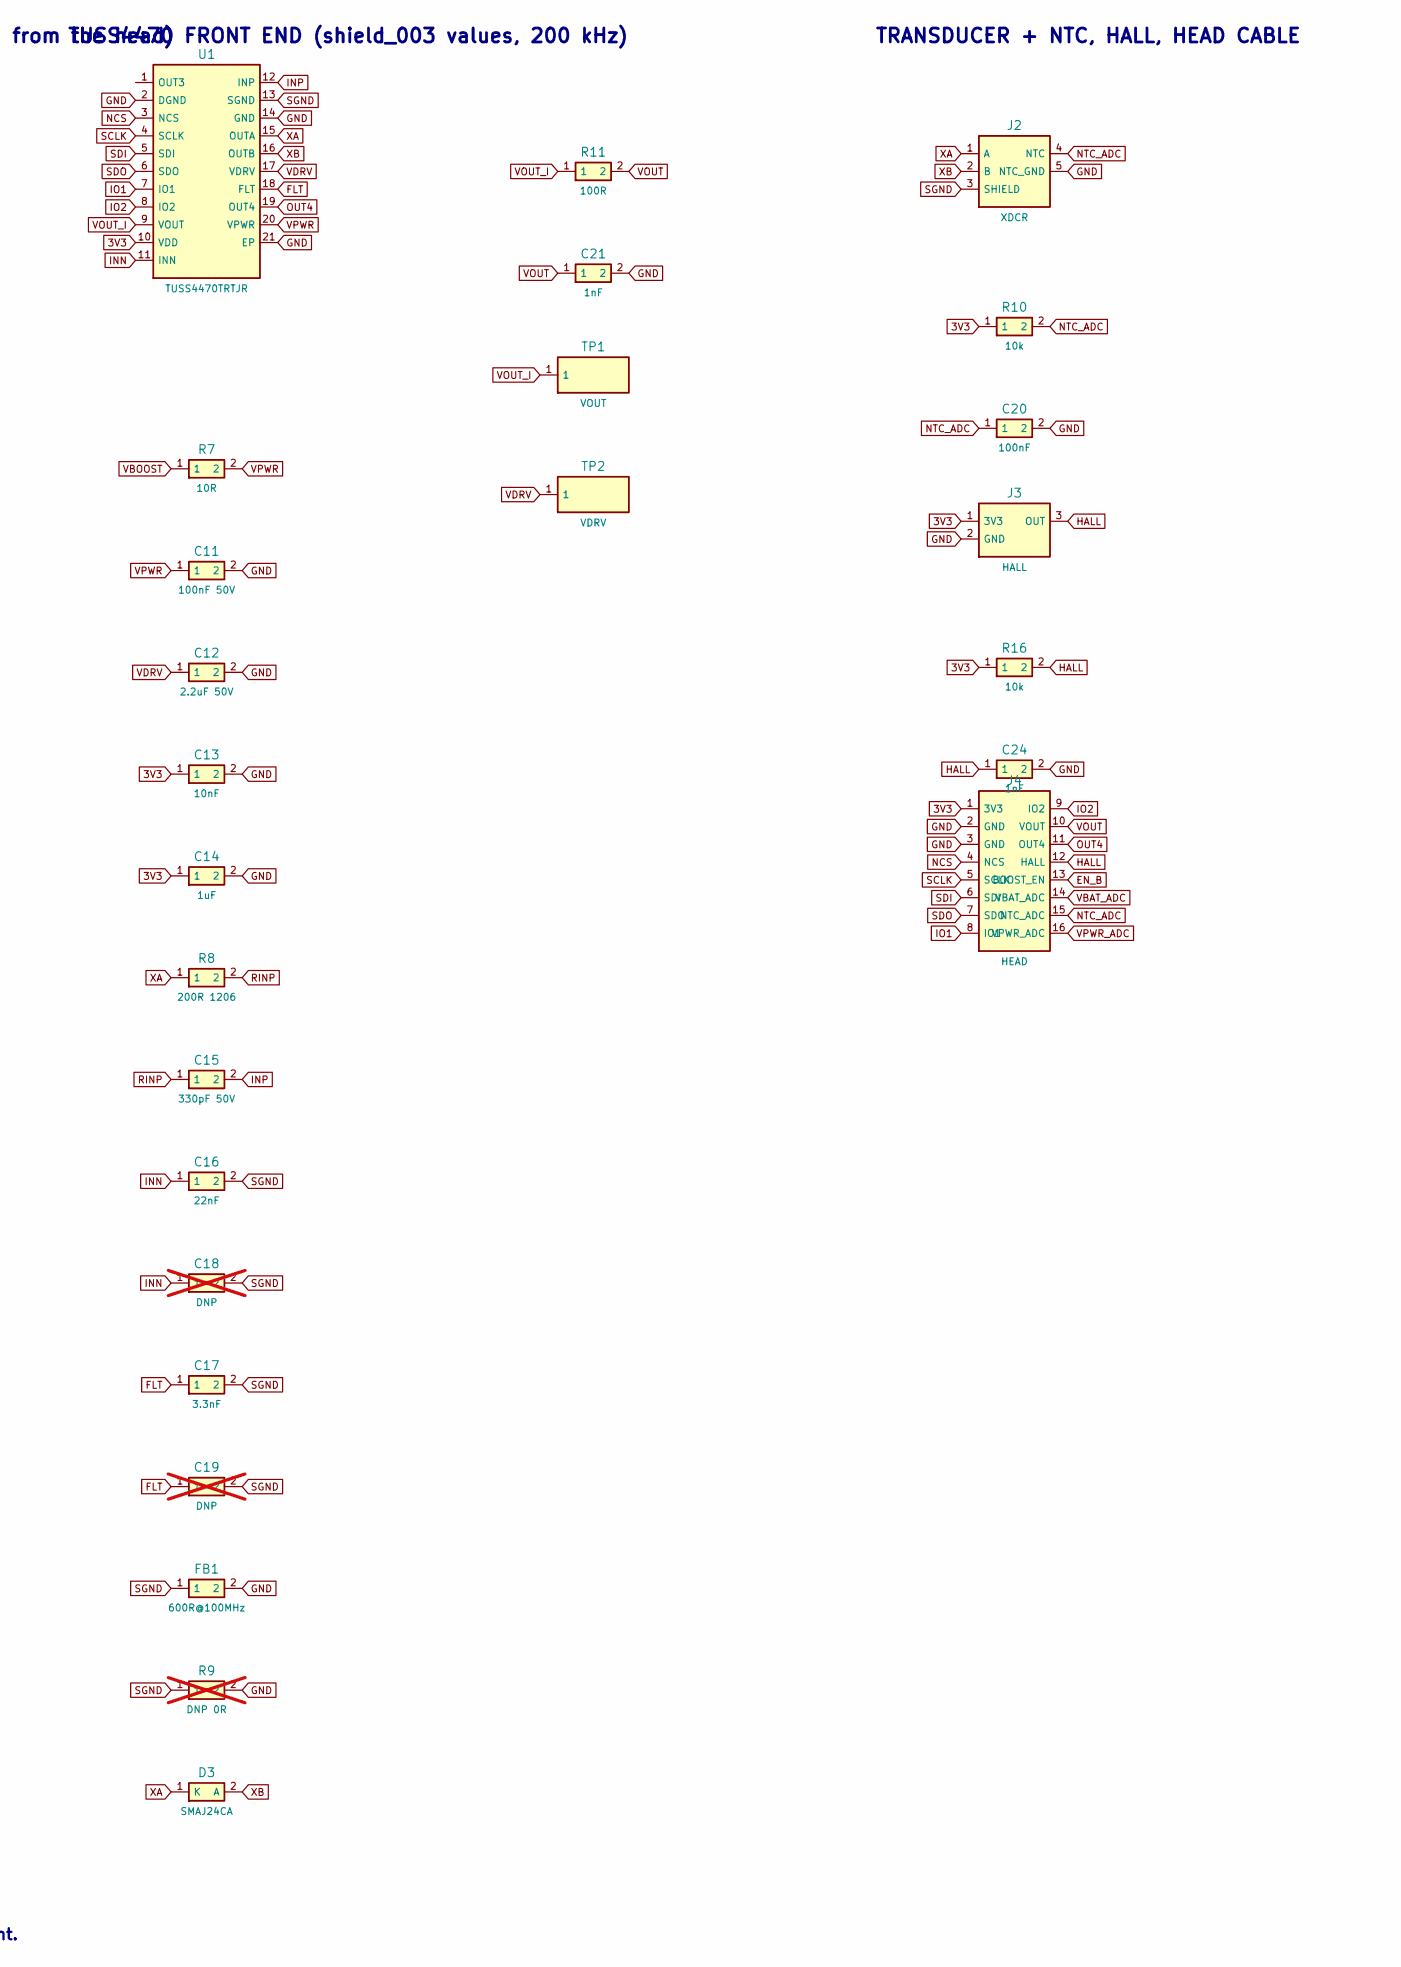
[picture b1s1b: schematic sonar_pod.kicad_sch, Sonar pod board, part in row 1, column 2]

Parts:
C1, C3, C4, C10: 10uF 10V; C_0805_2012Metric; LCSC C15850
C2, C20, C22, C23: 100nF; C_0603_1608Metric; LCSC C14663
C5, C6, C7: 22uF 6.3V; C_0805_2012Metric; LCSC C45783
C8, C9: 10uF 50V; C_1206_3216Metric; LCSC C13585
C11: 100nF 50V; C_0603_1608Metric; LCSC C14663
C12: 2.2uF 50V; C_1206_3216Metric; LCSC C50254
C13: 10nF; C_0603_1608Metric; LCSC C57112
C14: 1uF; C_0603_1608Metric; LCSC C15849
C15: 330pF 50V; C_0603_1608Metric; LCSC C1664
C16: 22nF; C_0603_1608Metric; LCSC C21122
C17: 3.3nF; C_0603_1608Metric; LCSC C1613
C18, C19: DNP; C_0603_1608Metric; not fitted
C21, C24: 1nF; C_0603_1608Metric; LCSC C1588
D1: PMEG6010ELR; Nexperia_CFP3_SOD-123W; LCSC C179432
D2: SMAJ24A; D_SMA; LCSC C129537
D3: SMAJ24CA; D_SMA; LCSC C129545
FB1: 600R@100MHz; L_0603_1608Metric; LCSC C1017
J1: BAT 3xL91; JST_XH_B2B-XH-A_1x02_P2.50mm_Vertical; LCSC C158012
J2: XDCR; JST_XH_B5B-XH-A_1x05_P2.50mm_Vertical; LCSC C144401
J3: HALL; JST_XH_B3B-XH-A_1x03_P2.50mm_Vertical; LCSC C144394
J4: HEAD; JST_PH_B16B-PH-K_1x16_P2.00mm_Vertical; LCSC C131338
L1: 22uH NR6028; L_Taiyo-Yuden_NR-60xx; LCSC C16218
L2: 1.5uH XFL4020; L_Coilcraft_XxL4020; LCSC C150393
Q1: AO3401A; SOT-23; LCSC C15127
R1, R6, R12, R13: 100k; R_0603_1608Metric; LCSC C25803
R2: 1M; R_0603_1608Metric; LCSC C22935
R3: 180k; R_0603_1608Metric; LCSC C25270
R4: 360k; R_0603_1608Metric; LCSC C23245
R5, R10, R15, R16: 10k; R_0603_1608Metric; LCSC C25804
R7: 10R; R_1206_3216Metric; LCSC C17903
R8: 200R 1206; R_1206_3216Metric; LCSC C25361
R9: DNP 0R; R_0603_1608Metric; not fitted
R11: 100R; R_0603_1608Metric; LCSC C22775
R14: 75k; R_0603_1608Metric; LCSC C23242
R17: 10R; R_0603_1608Metric; LCSC C25092
TP1: VOUT; TestPoint_Pad_1.5x1.5mm
TP2: VDRV; TestPoint_Pad_1.5x1.5mm
TP3: VBOOST; TestPoint_Pad_1.5x1.5mm
TP4: 3V3; TestPoint_Pad_1.5x1.5mm
TP5: GND; TestPoint_Pad_1.5x1.5mm
U1: TUSS4470TRTJR; QFN-20-1EP_4x4mm_P0.5mm_EP2.5x2.5mm_ThermalVias; LCSC C1855776
U2: TPS63020DSJR; Texas_DSJ0014A; LCSC C15483
U3: MT3608; SOT-23-6; LCSC C84817

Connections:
3V3: C5.1, C6.1, C7.1, C13.1, C14.1, J3.1 (3V3), J4.1 (3V3), R2.1, R10.1, R16.1, TP4.1, U1.10 (VDD), U2.4 (VOUT), U2.5 (VOUT)
EN_B: J4.13 (BOOST_EN), R6.2, U3.4 (EN)
FB_B: R4.2, R5.1, U3.3 (FB)
FB_T: R2.2, R3.1, U2.3 (FB)
FLT: C17.1, C19.1, U1.18 (FLT)
GND: C1.2, C2.2, C3.2, C4.2, C5.2, C6.2, C7.2, C8.2, C9.2, C10.2, C11.2, C12.2, C13.2, C14.2, C20.2, C21.2, C22.2, C23.2, C24.2, D2.2 (A), FB1.2, J1.2 (-), J2.5 (NTC_GND), J3.2 (GND), J4.2 (GND), J4.3 (GND), Q1.1 (G), R1.1, R3.2, R5.2, R9.2, R13.2, R15.2, TP5.1, U1.2 (DGND), U1.14 (GND), U1.21 (EP), U2.2 (GND), U2.13 (PS/SYNC), U2.15 (PGND), U3.2 (GND)
HALL: C24.1, J3.3 (OUT), J4.12 (HALL), R16.2
INN: C16.1, C18.1, U1.11 (INN)
INP: C15.2, U1.12 (INP)
IO1: J4.8 (IO1), U1.7 (IO1)
IO2: J4.9 (IO2), U1.8 (IO2)
NCS: J4.4 (NCS), U1.3 (NCS)
NTC_ADC: C20.1, J2.4 (NTC), J4.15 (NTC_ADC), R10.2
OUT4: J4.11 (OUT4), U1.19 (OUT4)
RINP: C15.1, R8.2
SCLK: J4.5 (SCLK), U1.4 (SCLK)
SDI: J4.6 (SDI), U1.5 (SDI)
SDO: J4.7 (SDO), U1.6 (SDO)
SGND: C16.2, C17.2, C18.2, C19.2, FB1.1, J2.3 (SHIELD), R9.1, U1.13 (SGND)
SW_B: D1.2 (A), L1.2, U3.1 (SW)
TL1: L2.1, U2.8 (L1), U2.9 (L1)
TL2: L2.2, U2.6 (L2), U2.7 (L2)
VB: C1.1, C3.1, C4.1, C10.1, L1.1, Q1.2 (S), R6.1, R12.1, R17.1, U2.10 (VIN), U2.11 (VIN), U2.12 (EN), U3.5 (IN)
VBAT: J1.1 (+), Q1.3 (D), R1.2
VBAT_ADC: C22.1, J4.14 (VBAT_ADC), R12.2, R13.1
VBOOST: C8.1, C9.1, D1.1 (K), D2.1 (K), R4.1, R7.1, R14.1, TP3.1
VDRV: C12.1, TP2.1, U1.17 (VDRV)
VINA: C2.1, R17.2, U2.1 (VINA)
VOUT: C21.1, J4.10 (VOUT), R11.2
VOUT_I: R11.1, TP1.1, U1.9 (VOUT)
VPWR: C11.1, R7.2, U1.20 (VPWR)
VPWR_ADC: C23.1, J4.16 (VPWR_ADC), R14.2, R15.1
XA: D3.1 (K), J2.1 (A), R8.1, U1.15 (OUTA)
XB: D3.2 (A), J2.2 (B), U1.16 (OUTB)

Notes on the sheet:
POWER IN + REVERSE PROTECTION + VBAT SENSE
3.3 V BUCK-BOOST (TPS63020)
22 V BOOST FOR VPWR (MT3608, EN from the head)
TUSS4470 FRONT END (shield_003 values, 200 kHz)
TRANSDUCER + NTC, HALL, HEAD CABLE
SONAR POD v0.1 - label-style schematic generated from design.py; nets connect by global label name.
Separate ESP32 (head) over J4. Boost 22 V -> TUSS4470 VPWR, VDRV regulated on-chip (knob vdrv 20).
VERIFY BEFORE ORDER: U2 footprint DSJ0014A (generated, pad geometry assumed), D1/D2 polarity, JST pin 1 orientation, L1/L2 saturation current.

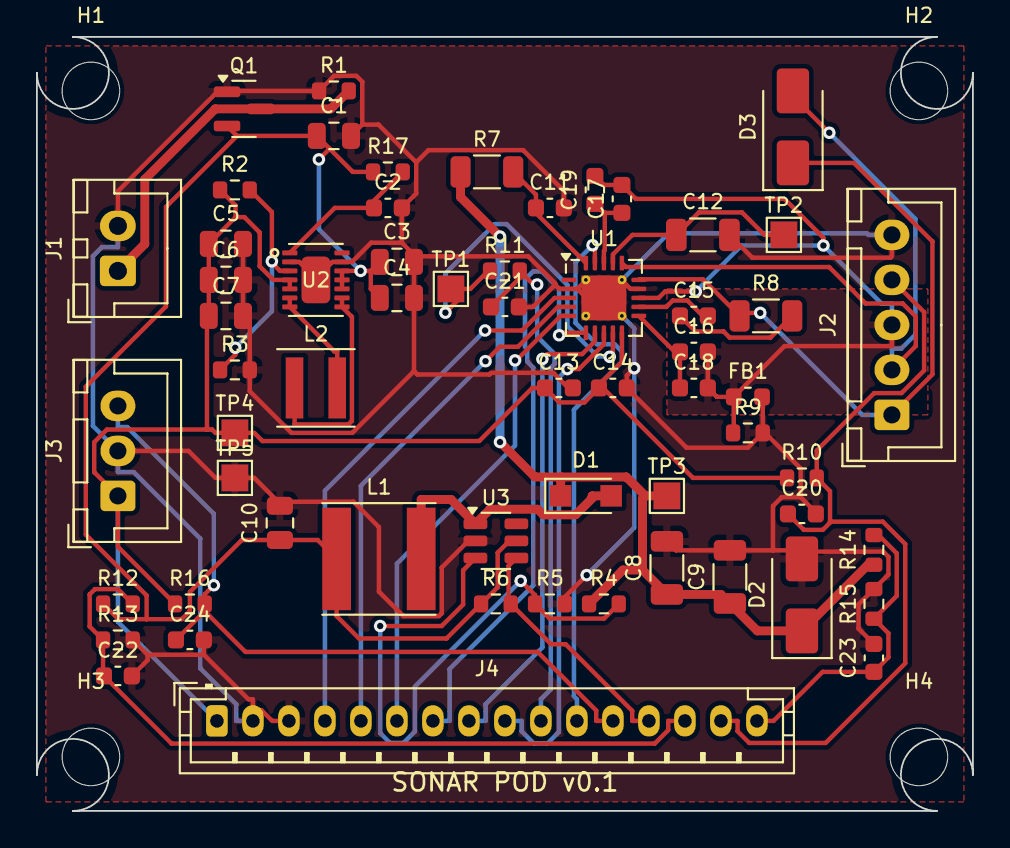
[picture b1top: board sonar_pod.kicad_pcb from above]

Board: 2 copper layers, 52.0 x 43.0 mm, 64 parts (0 on the bottom side), 34 nets.

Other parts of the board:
H1, H2, H3, H4: M3; MountingHole_3.2mm_M3

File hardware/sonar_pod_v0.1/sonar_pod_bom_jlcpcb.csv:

Comment,Designator,Footprint,LCSC Part #,MFR part,Note
BAT 3xL91,J1,JST_XH_B2B-XH-A_1x02_P2.50mm_Vertical,C158012,B2B-XH-A,"JST XH 2p, battery holder"
AO3401A,Q1,SOT-23,C15127,,P-FET reverse-battery (G=1 S=2 D=3)
100k,"R1,R6,R12,R13",R_0603_1608Metric,C25803,,Q1 gate
10uF 10V,"C1,C3,C4,C10",C_0805_2012Metric,C15850,,input bulk
TPS63020DSJR,U2,Texas_DSJ0014A,C15483,,"buck-boost 3.3 V 3 A; EN=VIN, PS/SYNC=GND (power save)"
1.5uH XFL4020,L2,L_Coilcraft_XxL4020,C150393,XFL4020-152MEB,Coilcraft XFL4020-152ME or equivalent 4x4 1.5uH >4 A
1M,R2,R_0603_1608Metric,C22935,,FB top (0.5 V ref -> 3.28 V)
180k,R3,R_0603_1608Metric,C25270,,FB bottom
100nF,"C2,C22,C23,C20",C_0603_1608Metric,C14663,,VINA bypass (max 0.22 uF)
10R,R17,R_0603_1608Metric,C25092,,VINA RC from VB
22uF 6.3V,"C5,C6,C7",C_0805_2012Metric,C45783,,VOUT
MT3608,U3,SOT-23-6,C84817,,"boost 22 V, EN pulled up, head can switch it"
22uH NR6028,L1,L_Taiyo-Yuden_NR-60xx,C16218,NR6028T220M,6x6 22 uH >1.5 A sat (same family as shield_003)
PMEG6010ELR,D1,Nexperia_CFP3_SOD-123W,C179432,,60 V 1 A Schottky (shield_003 part); K=1 A=2
10uF 50V,"C8,C9",C_1206_3216Metric,C13585,,boost out
360k,R4,R_0603_1608Metric,C23245,,FB top: 0.6*(1+360/10) = 22.2 V
10k,"R5,R15,R10,R16",R_0603_1608Metric,C25804,,FB bottom
SMAJ24A,D2,D_SMA,C129537,SMAJ24A,TVS 24 V standoff VBOOST (K=1) to GND (A=2)
TUSS4470TRTJR,U1,QFN-20-1EP_4x4mm_P0.5mm_EP2.5x2.5mm_ThermalVias,C1855776,,ultrasonic driver + log-amp receiver
10R,R7,R_1206_3216Metric,C17903,,RPWR (datasheet 8-1)
100nF 50V,C11,C_0603_1608Metric,C14663,,CPWR1 at pin 20
2.2uF 50V,C12,C_1206_3216Metric,C50254,,CPWR2 VDRV storage (shield: 2 uF 40 V)
10nF,C13,C_0603_1608Metric,C57112,,CVDD at pin 10
1uF,C14,C_0603_1608Metric,C15849,,VDD bulk
200R 1206,R8,R_1206_3216Metric,C25361,,RINP (1/4 W)
330pF 50V,C15,C_0603_1608Metric,C1664,,CINP
22nF,C16,C_0603_1608Metric,C21122,,CINN 200 kHz (1/(2*pi*150*f/4))
3.3nF,C17,C_0603_1608Metric,C1613,,CFLT 200 kHz (25/(2*pi*6250*f))
600R@100MHz,FB1,L_0603_1608Metric,C1017,BLM18PG601SN1D,SGND-GND ferrite (datasheet layout 10.1)
SMAJ24CA,D3,D_SMA,C129545,SMAJ24CA,bidirectional TVS across the transducer
100R,R11,R_0603_1608Metric,C22775,,VOUT series for the cable
1nF,"C21,C24",C_0603_1608Metric,C1588,,VOUT cable filter
75k,R14,R_0603_1608Metric,C23242,,VPWR x10/85 (shield_003)
XDCR,J2,JST_XH_B5B-XH-A_1x05_P2.50mm_Vertical,C144401,B5B-XH-A,"transducer A, B, shield; NTC, NTC gnd"
HALL,J3,JST_XH_B3B-XH-A_1x03_P2.50mm_Vertical,C144394,B3B-XH-A,US1881 on the arm
HEAD,J4,JST_PH_B16B-PH-K_1x16_P2.00mm_Vertical,C131338,B16B-PH-K-S,"to the ESP32 in the head, 16 wires"
